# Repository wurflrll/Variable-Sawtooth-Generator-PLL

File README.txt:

For another project I needed to generate variable frequency and amplitude sawtooth waveforms. Initially what I wanted was to make a small personal function
generator and interface for an 8-ohm speaker just for fun.  In the process I was thinking about having multiple channels, and in particular what if I wanted
to generate an additional sawtooth with given phase difference but identical frequency.  This I decided was enough for it's own PCB.  There are three reference 
signals: amplitude, frequency, and phase offset.  The circuit is analog and made out of discrete components, but an ESP32 & DAC is included if the user doesn't want 
to generate reference signals externally. The phase reference works by resetting channel 2 when channel 1 is equal to the phase reference.  The tricky part
is that the frequency of the two signals are determined by their 2 RC time constants.  I wanted the slope of channel 2 to match the slope of channel 1
irrespective of component tolerances (and for example without relying on example a small tolerance shunt resistor).  This circuit taught me a lot about 
hysteresis and the whole circuit is just one op-amp feedback circuit inside of another.  An LTSpice simulation file will be added as well.

The three ref signals:

Amplitude (AMP_REF): Identically determines amplitude (eg. 3V input creates 3V amplitude of Sawtooth)

Frequency (FREQ_REF): The FREQ_ref signals actually determines the slope of the sawtooth, where 1V input = 2V/millisecond slope
So the frequency equation is simply Frequency (in kHz) = 2 * FREQ / AMP_REF

Phase Offset: The phase offset is simply 360 degrees * PHASE_REF/AMP_REF (ie. frequency)

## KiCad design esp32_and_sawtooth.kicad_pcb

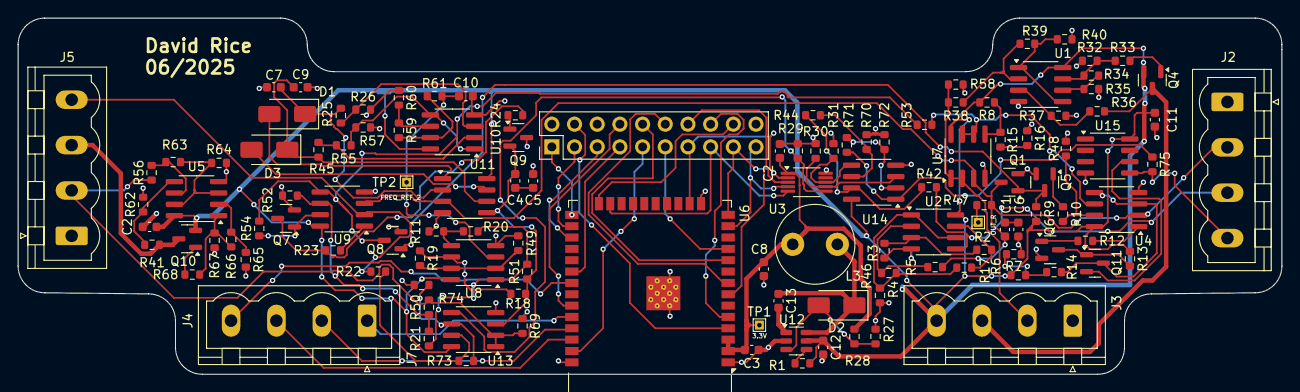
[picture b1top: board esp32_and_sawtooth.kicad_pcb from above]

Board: 2 copper layers, 141.5 x 39.9 mm, 124 parts (0 on the bottom side), 96 nets.

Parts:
C1, C2, C4, C5, C6, C11: 1uF; C_0603_1608Metric
C2#2, C7, C9: 100nF; C_0603_1608Metric
C3: 0.1uF; C_0603_1608Metric
C8, C10, C12: 10uF; C_0603_1608Metric
C13: 10nF; C_0603_1608Metric
D1, D2, D3: D; D_SMA
J2, J3, J4, J5: Conn_01x04_Socket; PhoenixContact_MSTBVA_2,5_4-G-5,08_1x04_P5.08mm_Vertical
J7: Conn_01x20_Socket; PinHeader_2x10_P2.54mm_Vertical
L3: 100uH; L_Radial_D8.7mm_P5.00mm_Fastron_07HCP
Q1, Q5, Q6, Q7, Q8, Q9: Q_NMOS_GSD; SOT-23
Q4, Q10, Q11: Q_PMOS_GSD; SOT-23
R1, R7, R10, R12, R13, R15, R16, R23, R24, R33, R35, R47, R51, R60, R65, R68: 1K; R_0603_1608Metric
R2, R3, R4, R5, R6, R8, R11, R17, R18, R19, R20, R21, R25, R26, R34, R36, R37, R38, R39, R41, R45, R55, R56, R59, R62, R63, R66: 100K; R_0603_1608Metric
R9, R14, R22, R28, R42, R44, R46, R50, R52, R53, R54, R61, R70, R71, R72, R73, R74, R75: 10K; R_0603_1608Metric
R27: 31.6K; R_0603_1608Metric
R29, R30, R31, R32, R40, R48, R49, R57, R58, R64, R67, R69: 16.9K; R_0603_1608Metric
TP1, TP2, TP3: TestPoint; TestPoint_THTPad_1.0x1.0mm_Drill0.5mm
U1, U2, U4, U5, U7, U8, U9, U10, U11, U13, U14, U15: NCS20072D; SOIC-8_3.9x4.9mm_P1.27mm
U3: MCP4728; MSOP-10_3x3mm_P0.5mm
U6: ESP32-WROOM-32E; ESP32-WROOM-32D
U12: AOZ1280CI; SOT-23-6

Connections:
+3.3V: C2#2.1, C3.1, C8.2, L3.2, R28.1, TP1.1, U3.1 (VDD), U6.2 (VDD), U6.3 (EN)
+BATT: C2.1, C11.1, C12.1, J3.4, Q4.2 (S), Q10.2 (S), R1.1, R6.2, R8.2, R9.1, R13.1, U1.8 (V+), U2.8 (V+), U4.8 (V+), U5.8 (V+), U7.8 (V+), U8.8 (V+), U9.8 (V+), U10.8 (V+), U11.8 (V+), U12.5 (VIN), U13.8 (V+), U14.8 (V+), U15.8 (V+)
AMP_REF: J2.4, R75.2, U15.5 (+)
AMP_REF_MIC: R71.1, R75.1, U14.1
CTS: J4.4, U6.31 (IO19)
DISCHARGE: Q1.1 (G), Q5.3 (D), Q8.1 (G), R9.2
FREQ_REF: J2.3, R42.1, U2.5 (+)
FREQ_REF2: C10.2, R61.2, TP2.1, U8.3 (+)
FREQ_REF_MIC: R42.2, R44.1, U14.7
GND: C2.2, C2#2.2, C3.2, C5.2, C6.2, C7.2, C8.1, C9.2, C10.1, C11.2, C12.2, J2.1, J3.1, J5.1, Q1.2 (S), Q5.2 (S), Q6.2 (S), Q7.2 (S), Q8.2 (S), Q9.3 (D), R3.1, R7.1, R11.1, R16.1, R26.2, R27.1, R29.2, R30.2, R31.2, R32.2, R35.2, R37.2, R40.1, R46.1, R48.1, R49.1, R52.1, R57.1, R58.2, R60.1, R62.2, R64.1, R65.2, R67.2, R69.1, R70.2, R72.2, R74.2, U1.4 (V-), U2.4 (V-), U3.10 (VSS), U4.4 (V-), U5.4 (V-), U6.1 (GND), U6.15 (GND), U6.38 (GND), U6.39 (GND), U7.4 (V-), U8.4 (V-), U9.4 (V-), U10.4 (V-), U11.4 (V-), U12.2 (GND), U13.4 (V-), U14.4 (V-), U15.4 (V-)
GPIO0: J7.1, U6.25 (IO0)
GPIO2: J7.18, U6.24 (IO2)
GPIO4: J7.3, U6.26 (IO4)
HYSTERESIS_FB: R12.1, U4.1
LDAC: J7.19, U3.4 (~LDAC), U6.13 (IO14)
unnamed: C1.2, C6.1
unnamed: C4.2, C5.1
unnamed: D1.2 (A), U11.1
unnamed: C7.1, D1.1 (K), R25.1, U11.2 (-)
unnamed: D2.2 (A), R27.2, R28.2, U12.3 (FB)
unnamed: C13.1, D2.1 (K), L3.1, U12.6 (LX)
unnamed: D3.2 (A), U11.7
unnamed: C9.1, D3.1 (K), R45.1, U11.6 (-)
unnamed: J7.5, U6.27 (IO16)
unnamed: J7.7, U6.30 (IO18)
unnamed: J7.8, U6.33 (IO21)
unnamed: J7.9, U6.37 (IO23)
unnamed: J7.10, U6.10 (IO25)
unnamed: J7.11, U6.11 (IO26)
unnamed: J7.12, U6.8 (IO32)
unnamed: J7.14, U6.7 (IO35)
unnamed: Q4.1 (G), R33.1
unnamed: Q5.1 (G), R10.2
unnamed: Q6.1 (G), R12.2
unnamed: Q7.3 (D), R23.1, R24.2
unnamed: Q7.1 (G), R54.1, U9.7
unnamed: Q8.3 (D), R53.1, R54.2, U9.5 (+)
unnamed: Q9.1 (G), R24.1
unnamed: Q10.1 (G), R68.1
unnamed: Q11.3 (D), R14.1, U4.3 (+), U4.5 (+)
unnamed: Q6.3 (D), Q11.1 (G), R13.2
unnamed: Q11.2 (S), U15.6 (-), U15.7
unnamed: R15.1, R16.2
unnamed: R23.2, U9.1
unnamed: R32.1, R33.2, R34.1, U1.7
unnamed: R59.2, R61.1, U10.7
unnamed: R66.1, R67.1, R68.2, U5.1
unnamed: R36.2, R37.1, U1.3 (+)
unnamed: R38.2, R39.1, U1.2 (-)
unnamed: R39.2, R40.2, U1.1, U1.5 (+)
unnamed: R34.2, R35.1, U1.6 (-)
unnamed: R2.1, R3.2, U2.3 (+)
unnamed: R4.1, R5.1, U2.2 (-)
unnamed: R4.2, R17.1, R46.2, U2.1, U2.6 (-)
unnamed: R63.2, R64.2, U5.3 (+), U5.7
unnamed: R65.1, R66.2, U5.2 (-)
unnamed: R41.2, R62.1, U5.5 (+)
unnamed: R56.2, R63.1, U5.6 (-)
unnamed: R8.1, R15.2, U7.5 (+)
unnamed: R19.2, R49.2, U8.2 (-), U8.7
unnamed: R11.2, R20.1, U8.5 (+)
unnamed: R18.1, R19.1, U8.6 (-)
unnamed: R21.1, R50.1, R52.2, U9.6 (-)
unnamed: R25.2, R26.1, U10.3 (+)
unnamed: R45.2, R55.1, U10.2 (-)
unnamed: R55.2, R57.2, U10.1, U10.5 (+)
unnamed: R59.1, R60.2, U10.6 (-)
unnamed: C13.2, U12.1 (BST)
unnamed: R1.2, U12.4 (EN)
unnamed: R29.1, U3.6 (VOUTA), U13.5 (+)
unnamed: R73.2, R74.1, U13.6 (-)
unnamed: R30.1, U3.7 (VOUTB), U14.3 (+)
unnamed: R71.2, R72.1, U14.2 (-)
unnamed: R31.1, U3.8 (VOUTC), U14.5 (+)
unnamed: R44.2, R70.1, U14.6 (-)
OUTPUT1: C1.1, J2.2, Q1.3 (D), R5.2, R47.1, U4.2 (-), U7.3 (+), U9.3 (+), U11.3 (+)
OUTPUT1_BUFFERED: J3.2, R38.1, R58.1, U7.1, U7.2 (-)
OUTPUT2: C4.1, Q9.2 (S), R18.2, R51.1, U11.5 (+), U13.3 (+)
OUTPUT2_BUFFERED: J5.2, R50.2, R56.1, R69.2, U13.1, U13.2 (-)
OUT_R: R2.2, R17.2, R47.2, TP3.1, U2.7
OUT_R2: R20.2, R21.2, R51.2, U8.1
PHASE_REF: J5.4, R22.2, U9.2 (-)
PHASE_REF_MIC: R22.1, R73.1, U13.7
RDY: J7.15, U3.5 (RDY/~BSY), U6.23 (IO15)
REF_0_1: R6.1, R7.2, R14.2
REF_0_2: R53.2, U4.6 (-), U7.6 (-), U7.7
RTS: J4.3, U6.36 (IO22)
RXD: J4.1, U6.34 (RXD0/IO3)
SCL: J7.17, U3.2 (SCL), U6.14 (IO12)
SDA: J7.13, U3.3 (SDA), U6.16 (IO13)
SENSOR_VN: J7.16, U6.5 (SENSOR_VN)
SENSOR_VP: J7.4, U6.4 (SENSOR_VP)
TXD: J4.2, U6.35 (TXD0/IO1)
V_LOAD1: J3.3, Q4.3 (D), R36.1
V_LOAD2: J5.3, Q10.3 (D), R41.1
~DISCHARGE: R10.1, R48.2, U4.7

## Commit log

2025-06-29 Add files via upload
    Adding Original KiCad Files
2026-03-20 Update Discriptions / Add Screenshots of Schematics
2026-03-20 Fix Project Folder
